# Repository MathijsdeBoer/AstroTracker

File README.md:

# AstroTracker
Astrotracker designed to be produced with a 3D printer

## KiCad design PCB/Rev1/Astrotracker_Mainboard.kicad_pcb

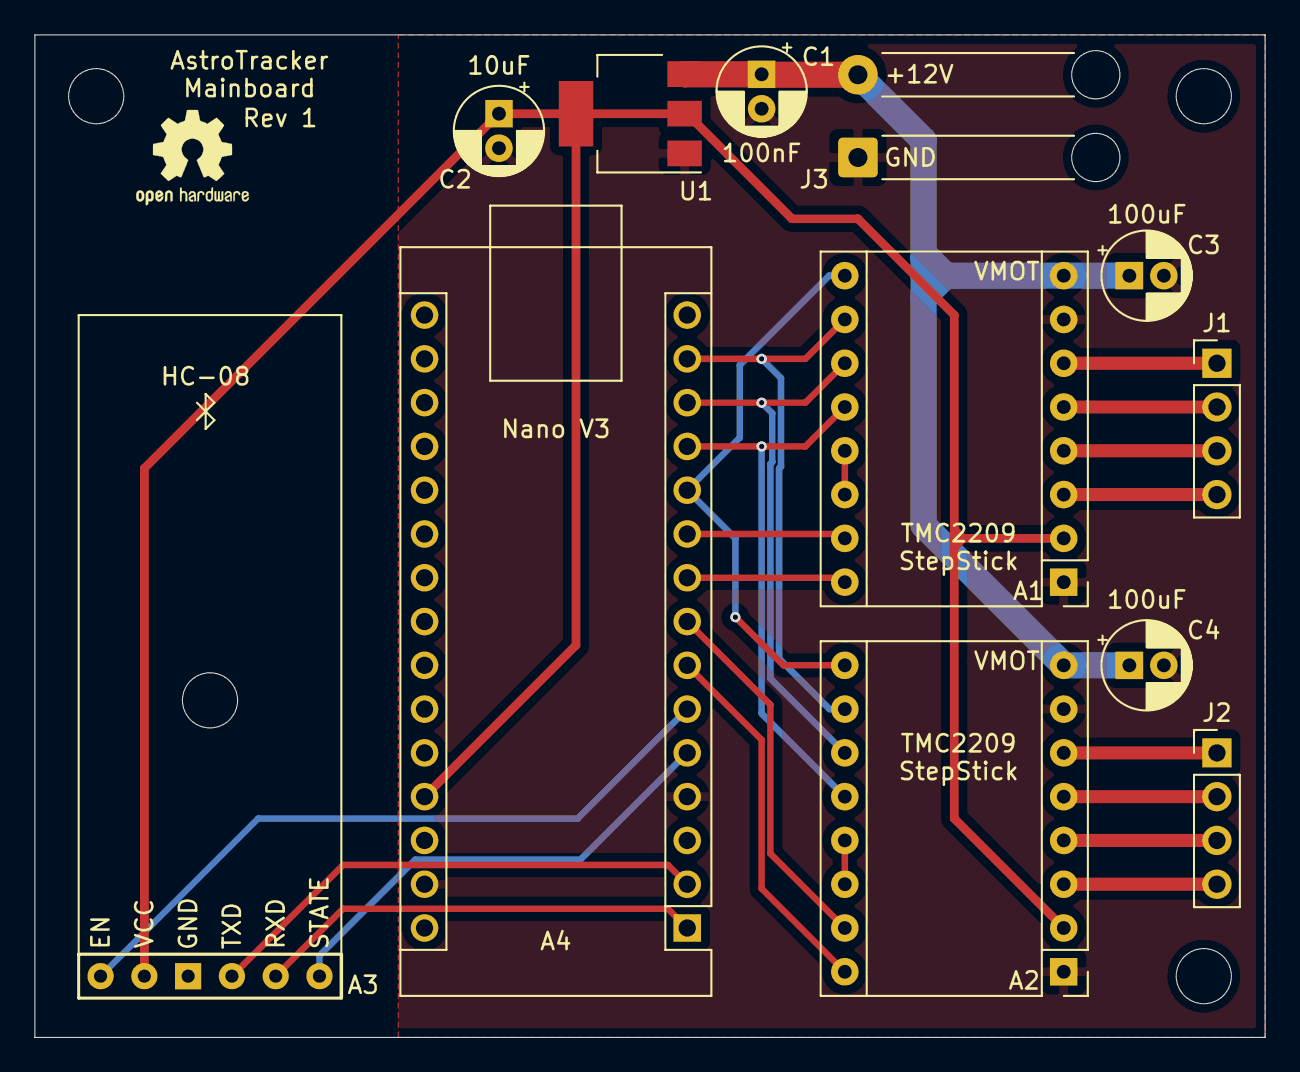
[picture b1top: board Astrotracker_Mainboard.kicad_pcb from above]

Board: 2 copper layers, 71.4 x 58.2 mm, 16 parts (0 on the bottom side), 25 nets.

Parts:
A1, A2: Pololu_Breakout_A4988; Pololu_Breakout-16_15.2x20.3mm
A3: HC-08; HC08-Breakout
A4: Arduino_Nano_v3.x; Arduino_Nano
C1: 100nF; CP_Radial_D5.0mm_P2.00mm
C2: 10uF; CP_Radial_D5.0mm_P2.00mm
C3, C4: 100uF; CP_Radial_D5.0mm_P2.00mm
H1, H2, H3, H4: MountingHole; MountingHole_3.2mm_M3
J1, J2: Conn_01x04; PinHeader_1x04_P2.54mm_Vertical
J3: Conn_01x02_Male; SolderWire-0.5sqmm_1x02_P4.8mm_D0.9mm_OD2.3mm_Relief
U1: LD1117S50TR_SOT223; SOT-223-3_TabPin2

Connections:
+5V: A1.2, A2.2, A3.5, A4.27, C2.1, U1.2
+12V: A1.8, A2.8, C1.1, C3.1, C4.1, J3.2, U1.3
GND: A1.1, A1.7, A2.1, A2.7, A3.4, A4.4, A4.29, C1.2, C2.2, C3.2, C4.2, J3.1, U1.1
M1DIR: A1.16, A4.9
M1STEP: A1.15, A4.10
M2DIR: A2.16, A4.7
M2STEP: A2.15, A4.8
MOT_EN: A1.9, A2.9, A4.11
MS1: A1.10, A2.10, A4.14
MS2: A1.11, A2.11, A4.13
MS3: A1.12, A2.12, A4.12
unnamed: A1.3, J1.4
unnamed: A1.4, J1.3
unnamed: A1.5, J1.2
unnamed: A1.6, J1.1
unnamed: A1.13, A1.14
unnamed: A2.3, J2.4
unnamed: A2.4, J2.3
unnamed: A2.5, J2.2
unnamed: A2.6, J2.1
unnamed: A2.13, A2.14
unnamed: A3.1, A4.5
unnamed: A3.2, A4.1
unnamed: A3.3, A4.2
unnamed: A3.6, A4.6

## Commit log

2020-09-10 Initial PCB commit
2020-09-10 Move PCB files to own subdirectory
2020-09-13 Move files around
2020-09-18 Arduino Mega based mainboard
2021-04-07 Clean out repo for a restart
2021-04-07 Add Introduction
2021-04-08 Adjust image sizes Add a small bit of text
2021-04-08 Update Introduction
2021-04-09 Licenses
2021-04-09 Update licensing explanation
2021-04-11 Formatting, some extra explanation
2021-04-11 Add our design goals and considerations
2021-04-13 Add Gitignore
2021-04-13 Add placeholder Electronics project
2021-04-13 Add entry on motors
2021-04-13 Also include the Pico Library's images for Readme
2021-04-16 Expand on some topics
2021-04-16 WIP version of gears related writeup
2021-04-16 Fix a typo
2021-04-17 Fix self-referral
2021-04-17 Added "We have the dumb, please help" text
2021-04-17 Gears post updated
2021-04-18 More explanation on our gearbox
2021-04-20 First basic gearbox design
